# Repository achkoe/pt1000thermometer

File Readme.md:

See doc/pt1000thermometer.pdf for some description of this project.

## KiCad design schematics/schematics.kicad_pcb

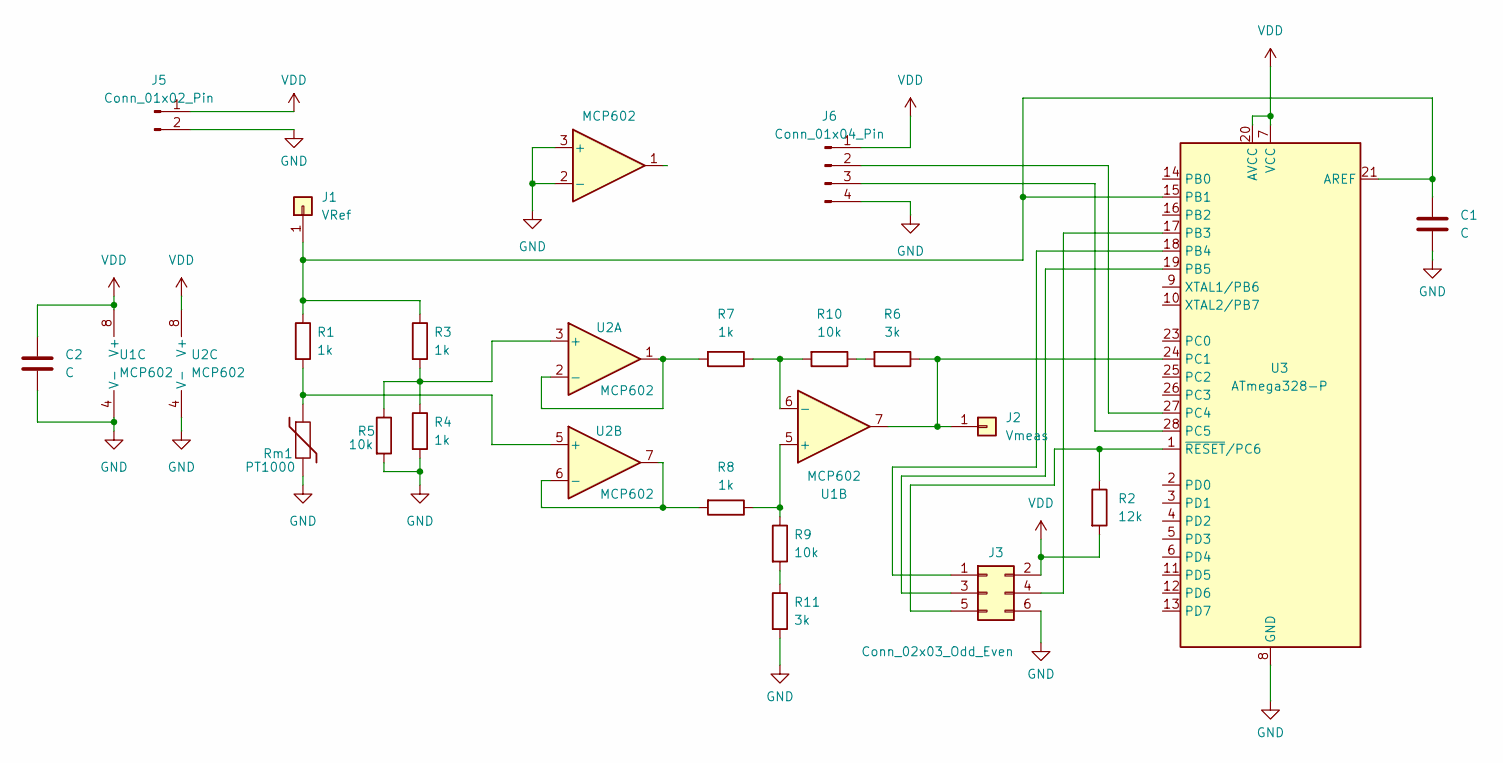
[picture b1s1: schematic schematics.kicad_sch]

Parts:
C1, C2: C; CP_Axial_L10.0mm_D4.5mm_P15.00mm_Horizontal
J1: VRef; Pin_D1.0mm_L10.0mm
J2: Vmeas; Pin_D1.0mm_L10.0mm
J3: Conn_02x03_Odd_Even; PinHeader_2x03_P2.54mm_Vertical
J5: Conn_01x02_Pin; PinHeader_1x02_P2.54mm_Vertical
J6: Conn_01x04_Pin; PinHeader_1x04_P2.54mm_Vertical
R1, R3, R4, R7, R8: 1k; R_Axial_DIN0207_L6.3mm_D2.5mm_P10.16mm_Horizontal
R2: 12k; R_Axial_DIN0207_L6.3mm_D2.5mm_P10.16mm_Horizontal
R5, R9, R10: 10k; R_Axial_DIN0207_L6.3mm_D2.5mm_P10.16mm_Horizontal
R6, R11: 3k; R_Axial_DIN0207_L6.3mm_D2.5mm_P10.16mm_Horizontal
Rm1: PT1000; R_Axial_DIN0204_L3.6mm_D1.6mm_P2.54mm_Vertical
U1, U2: MCP602; DIP-8_W7.62mm
U3: ATmega328-P; DIP-28_W7.62mm

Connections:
GND: C1.2, C2.2, J3.6, J5.2, J6.4, R4.2, R5.2, R11.2, Rm1.2, U1.2 (-), U1.3 (+), U1.4 (V-), U2.4 (V-), U3.8 (GND), U3.22 (GND)
unnamed: C1.1, J1.1, R1.1, R3.1, U3.15 (PB1), U3.21 (AREF)
unnamed: J2.1, R6.1, U1.7, U3.24 (PC1)
unnamed: J3.1, U3.18 (PB4)
unnamed: J3.3, U3.19 (PB5)
unnamed: J3.4, U3.17 (PB3)
unnamed: J3.5, R2.1, U3.1 (~RESET/PC6)
unnamed: J6.2, U3.27 (PC4)
unnamed: J6.3, U3.28 (PC5)
unnamed: R6.2, R10.1
unnamed: R9.2, R11.1
unnamed: R8.1, R9.1, U1.5 (+)
unnamed: R7.1, R10.2, U1.6 (-)
unnamed: R3.2, R4.1, R5.1, U2.3 (+)
unnamed: R7.2, U2.1, U2.2 (-)
unnamed: R1.2, Rm1.1, U2.5 (+)
unnamed: R8.2, U2.6 (-), U2.7
VDD: C2.1, J3.2, J5.1, J6.1, R2.2, U1.8 (V+), U2.8 (V+), U3.7 (VCC), U3.20 (AVCC)

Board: 2 copper layers, 22 parts (0 on the bottom side), 18 nets, no tracks yet.

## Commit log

2024-01-11 initial checkin
2024-01-11 added Readme.md
